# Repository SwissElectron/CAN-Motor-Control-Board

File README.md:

# **OpenSource CAN FD Compatible Motor Board**

This Board was designed as a part of a larger project in the making for a Robotic Arm Actuator System. The board can manipulate a BLDC motor from 24V to 48V (designed around LiPo battery packs) and with a max current rating of 20 A. 

## Board Information
- STM32F103 Central Microcontroller
- Sensor-less or Wioth Sensor Control strategies 
- 24V to 48V - 20 A
- Optional 5V rail for powering sensors on the CAN Bus

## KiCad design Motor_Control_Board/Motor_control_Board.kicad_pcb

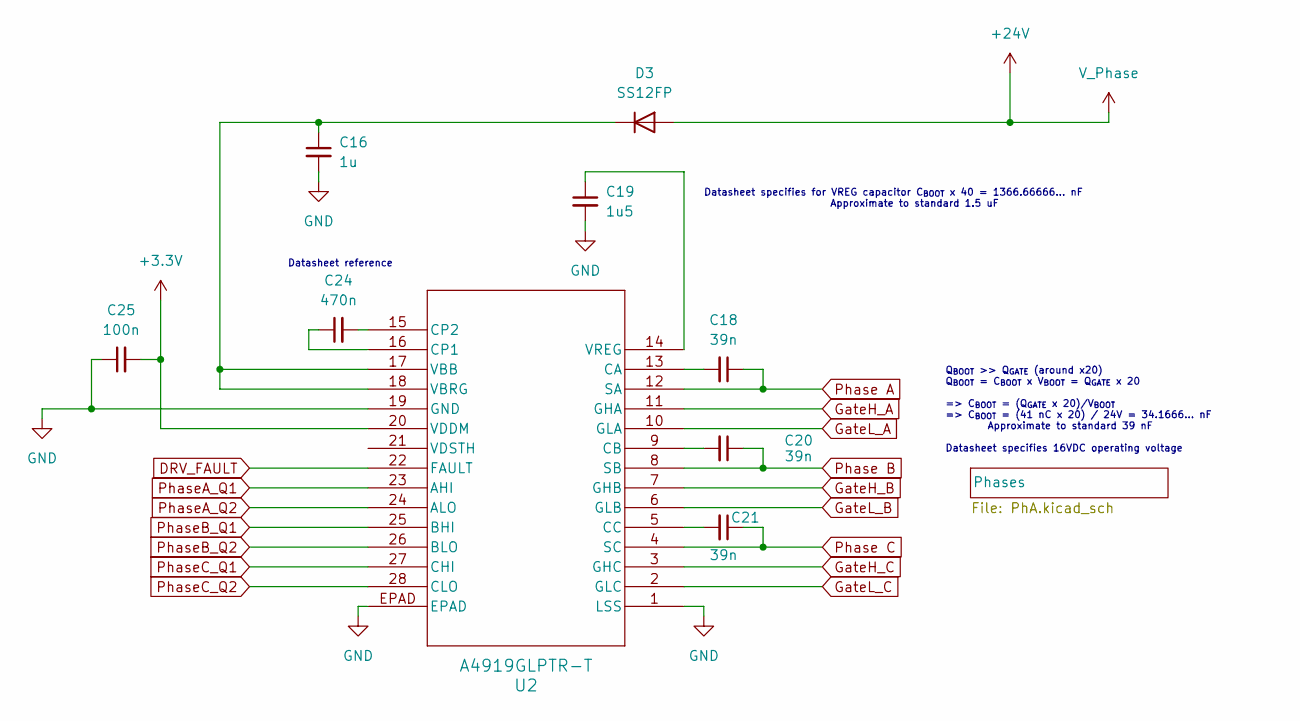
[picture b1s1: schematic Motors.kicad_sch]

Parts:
C16: 1u; C_0402_1005Metric; PartNum C1005X5R1C155K050BC
C18, C20, C21: 39n; C_0402_1005Metric; PartNum C0402C393J4RACTU
C19: 1u5; C_0402_1005Metric; PartNum C1005X5R1C155K050BC
C24: 470n; C_0603_1608Metric; PartNum CL10B474KO8NNWC
C25: 100n; C_0402_1005Metric; PartNum C0402C104K4PAC
D3: SS12FP; DIO_SS12LS_RVG; PartNum SS12FP
U2: A4919GLPTR-T; A4919GLPTR-T_ALM; PartNum A4919GLPTR-T

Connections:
+3.3V: C25.2, U2.20 (VDDM); also elsewhere on the board
DRV_FAULT: U2.22 (FAULT); also elsewhere on the board
GND: C16.2, C19.2, C25.1, U2.1 (LSS), U2.19 (GND), U2.EPAD; also elsewhere on the board
GateH_A: U2.11 (GHA); also elsewhere on the board
GateH_B: U2.7 (GHB); also elsewhere on the board
GateH_C: U2.3 (GHC); also elsewhere on the board
GateL_A: U2.10 (GLA); also elsewhere on the board
GateL_B: U2.6 (GLB); also elsewhere on the board
GateL_C: U2.2 (GLC); also elsewhere on the board
unnamed: C16.1, D3.1 (K), U2.17 (VBB), U2.18 (VBRG)
unnamed: C18.2, U2.13 (CA)
unnamed: C20.2, U2.9 (CB)
unnamed: C21.2, U2.5 (CC)
unnamed: C24.1, U2.16 (CP1)
unnamed: C24.2, U2.15 (CP2)
unnamed: C19.1, U2.14 (VREG)
Phase A: C18.1, U2.12 (SA); also elsewhere on the board
Phase B: C20.1, U2.8 (SB); also elsewhere on the board
Phase C: C21.1, U2.4 (SC); also elsewhere on the board
PhaseA_Q1: U2.23 (AHI); also elsewhere on the board
PhaseA_Q2: U2.24 (ALO); also elsewhere on the board
PhaseB_Q1: U2.25 (BHI); also elsewhere on the board
PhaseB_Q2: U2.26 (BLO); also elsewhere on the board
PhaseC_Q1: U2.27 (CHI); also elsewhere on the board
PhaseC_Q2: U2.28 (CLO); also elsewhere on the board

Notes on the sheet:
Q_{BOOT} >> Q_{GATE} (around x20) Q_{BOOT} = C_{BOOT} x V_{BOOT} = Q_{GATE} x 20 => C_{BOOT} = (Q_{GATE} x 20)/V_{BOOT} => C_{BOOT} = (41 nC x 20) / 24V = 34.1666... nF Approximate to standard 39 nF Datasheet specifies 16VDC operating voltage
Datasheet reference
Datasheet specifies for VREG capacitor C_{BOOT} x 40 = 1366.66666... nF Approximate to standard 1.5 uF

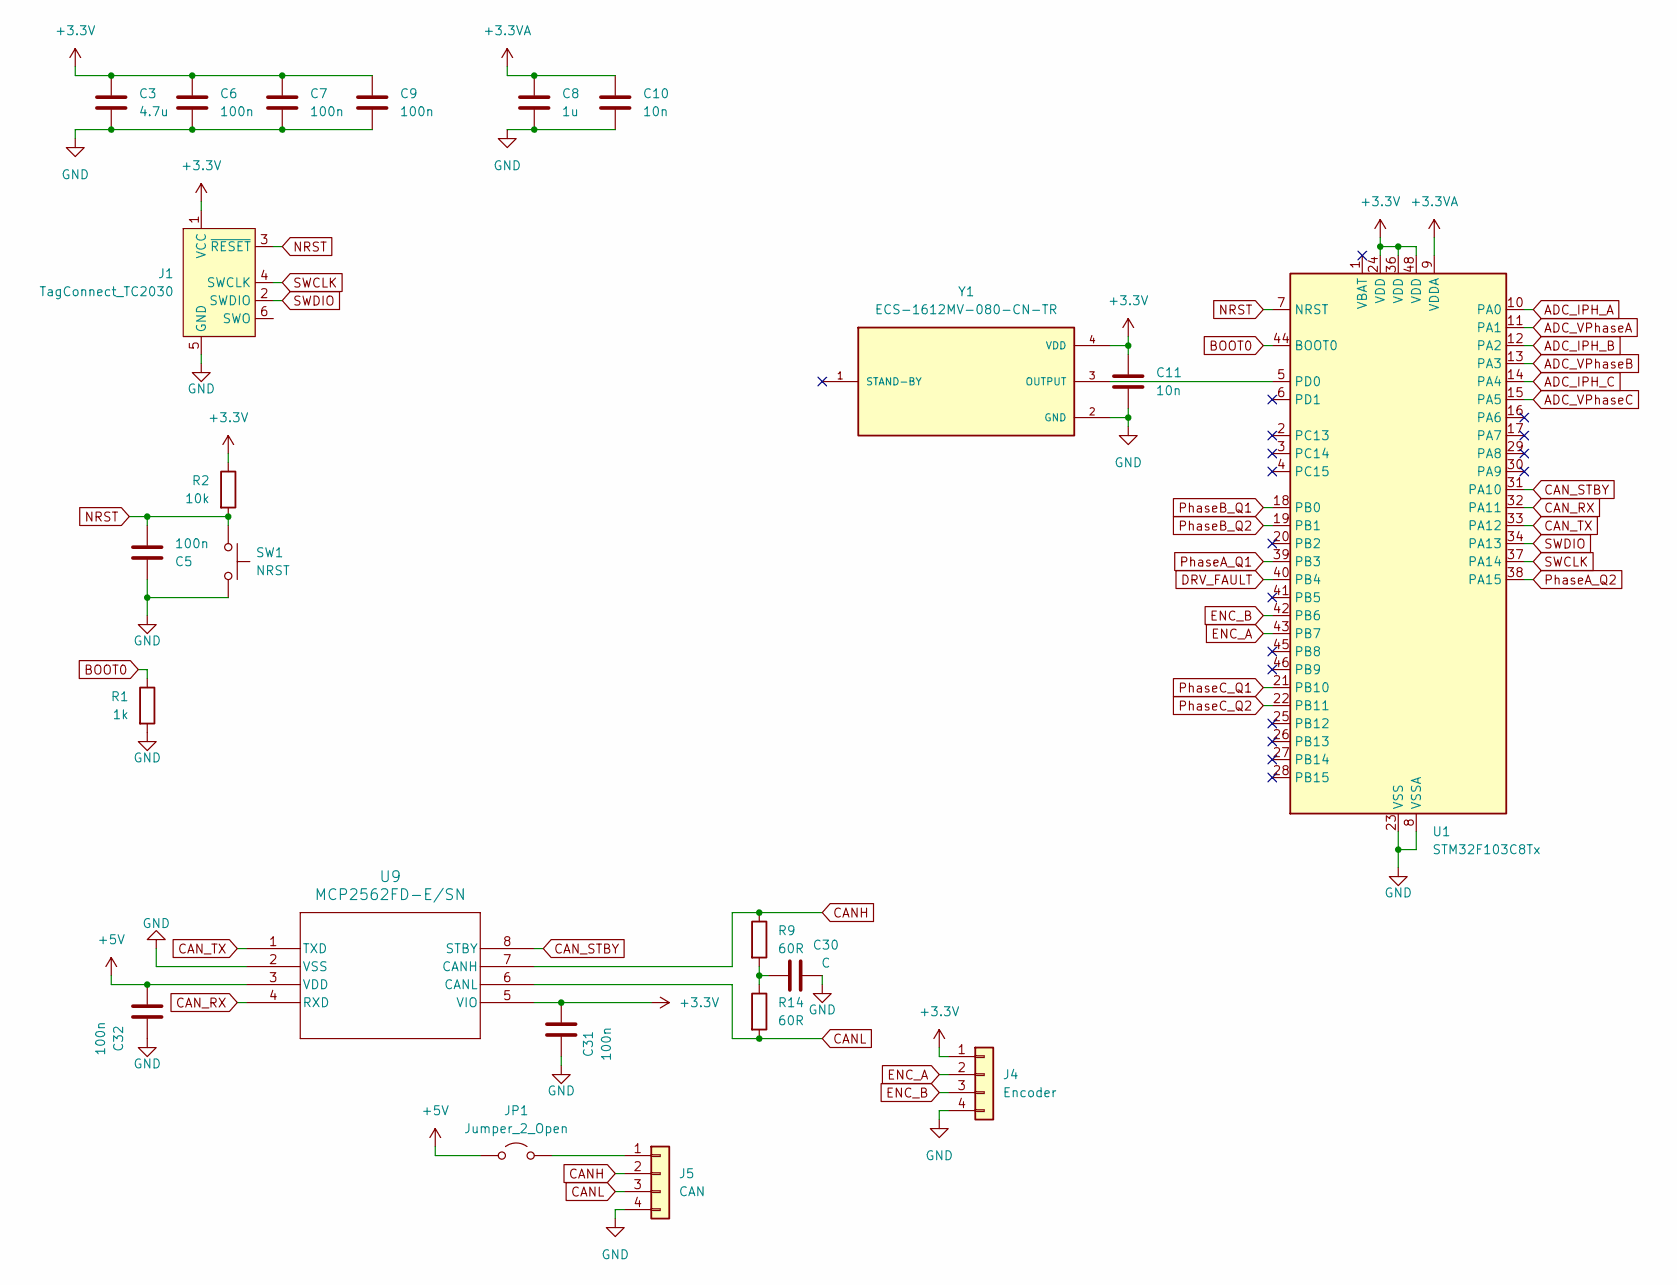
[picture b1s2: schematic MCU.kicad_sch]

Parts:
C3: 4.7u; C_0603_1608Metric; PartNum C0603C475M9PAC
C5, C6, C7, C9: 100n; C_0402_1005Metric; PartNum C0402C104K4PAC
C8: 1u; C_0402_1005Metric; PartNum GMD155R60J105KE11D
C10, C11: 10n; C_0402_1005Metric; PartNum GMD155R60J105KE11D
C30: C; C_0402_1005Metric
C31: 100n; C_0402_1005Metric; PartNum C0402C104K8RAC
C32: 100n; C_0402_1005Metric; PartNum GRM155R60J104MA01J
J1: TagConnect_TC2030; Tag-Connect_TC2030-IDC-NL_2x03_P1.27mm_Vertical
J4: Encoder; Molex_Pico-Clasp_501331-0407_1x04-1MP_P1.00mm_Vertical
J5: CAN; Molex_Pico-Clasp_501331-0407_1x04-1MP_P1.00mm_Vertical
JP1: Jumper_2_Open; SolderJumper-2_P1.3mm_Open_TrianglePad1.0x1.5mm
R1: 1k; C_0402_1005Metric; PartNum 0402WGF1001TCE
R2: 10k; R_0402_1005Metric; PartNum 0402WGF1002TCE
R9, R14: 60R; R_0402_1005Metric; PartNum 560112110170
SW1: NRST; NANOT100AS; PartNum NANOT100AS
U1: STM32F103C8Tx; LQFP-48_7x7mm_P0.5mm; PartNum STM32F103C8T7
U9: MCP2562FD-E/SN; MCP2562FD-ESN; PartNum MCP2562FD-E/SN
Y1: ECS-1612MV-080-CN-TR; OSC_ECS-1612MV-080-CN-TR-4; PartNum ECS-1612MV-080-CN-TR

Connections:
+3.3V: C3.1, C6.1, C7.1, C9.1, C11.1, C31.2, J1.1 (VCC), J4.1, R2.1, U1.24 (VDD), U1.36 (VDD), U1.48 (VDD), U9.5 (VIO), Y1.4 (VDD); also elsewhere on the board
+3.3VA: C8.1, C10.1, U1.9 (VDDA); also elsewhere on the board
+5V: C32.1, JP1.1 (A), U9.3 (VDD); also elsewhere on the board
ADC_IPH_A: U1.10 (PA0); also elsewhere on the board
ADC_IPH_B: U1.12 (PA2); also elsewhere on the board
ADC_IPH_C: U1.14 (PA4); also elsewhere on the board
ADC_VPhaseA: U1.11 (PA1); also elsewhere on the board
ADC_VPhaseB: U1.13 (PA3); also elsewhere on the board
ADC_VPhaseC: U1.15 (PA5); also elsewhere on the board
BOOT0: R1.1, U1.44 (BOOT0)
CANH: J5.2, R9.1, U9.7 (CANH)
CANL: J5.3, R14.2, U9.6 (CANL)
CAN_RX: U1.32 (PA11), U9.4 (RXD)
CAN_STBY: U1.31 (PA10), U9.8 (STBY)
CAN_TX: U1.33 (PA12), U9.1 (TXD)
DRV_FAULT: U1.40 (PB4); also elsewhere on the board
ENC_A: J4.2, U1.43 (PB7)
ENC_B: J4.3, U1.42 (PB6)
GND: C3.2, C5.1, C6.2, C7.2, C8.2, C9.2, C10.2, C11.2, C30.2, C31.1, C32.2, J1.5 (GND), J4.4, J5.4, R1.2, SW1.2, U1.8 (VSSA), U1.23 (VSS), U1.35 (VSS), U1.47 (VSS), U9.2 (VSS), Y1.2 (GND); also elsewhere on the board
NRST: C5.2, J1.3 (~RESET), R2.2, SW1.1, U1.7 (NRST)
unnamed: C30.1, R9.2, R14.1
unnamed 31: J5.1, JP1.2 (B); also elsewhere on the board
unnamed: U1.5 (PD0), Y1.3 (OUTPUT)
PhaseA_Q1: U1.39 (PB3); also elsewhere on the board
PhaseA_Q2: U1.38 (PA15); also elsewhere on the board
PhaseB_Q1: U1.18 (PB0); also elsewhere on the board
PhaseB_Q2: U1.19 (PB1); also elsewhere on the board
PhaseC_Q1: U1.21 (PB10); also elsewhere on the board
PhaseC_Q2: U1.22 (PB11); also elsewhere on the board
SWCLK: J1.4 (SWCLK), U1.37 (PA14)
SWDIO: J1.2 (SWDIO), U1.34 (PA13)

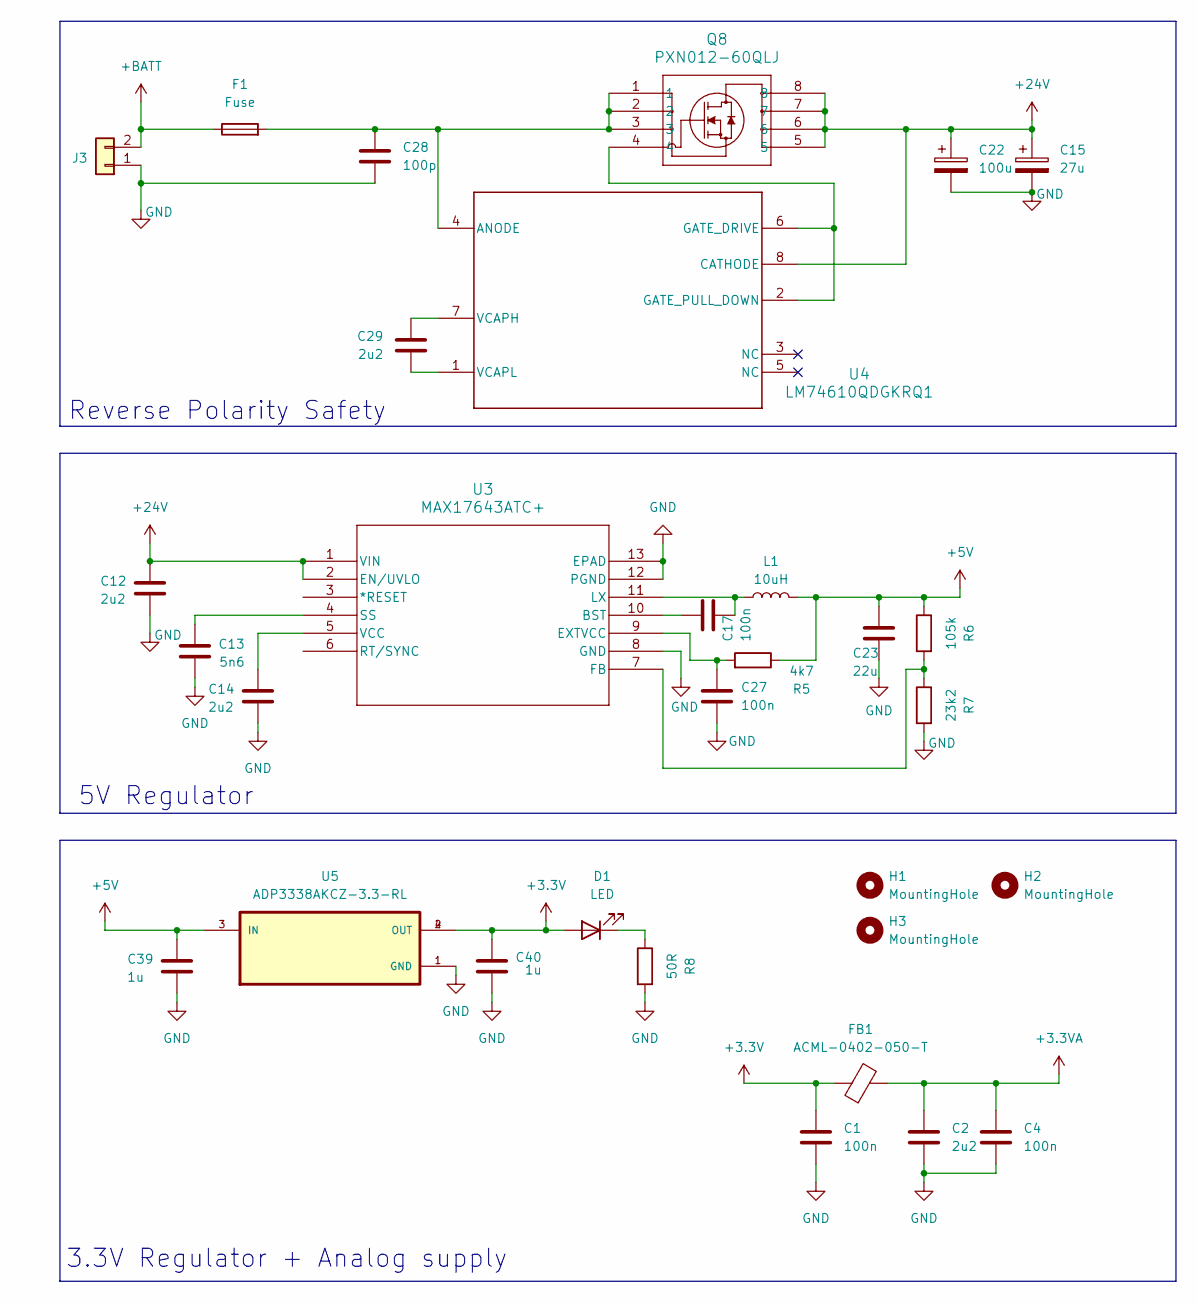
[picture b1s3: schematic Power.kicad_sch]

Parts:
C1, C4: 100n; C_0402_1005Metric; PartNum GCM1555C1H240FA16J
C2: 2u2; C_1206_3216Metric; PartNum C1206C225M5REC7210
C12: 2u2; C_1210_3225Metric; PartNum GRM32ER72A225KA35L
C13: 5n6; C_0402_1005Metric; PartNum GMD155R60J105KE11D
C14, C29: 2u2; C_0603_1608Metric; PartNum GRM188R71A225KE15
C15: 27u; CP_Elec_6.3x7.7; PartNum UUD1H270MCL1GS
C17, C27: 100n; C_0402_1005Metric; PartNum GMD155R60J105KE11D
C22: 100u; CP_Elec_8x10; PartNum UWT1H101MNL1GS
C23: 22u; C_1210_3225Metric; PartNum GRM32ER71C226KEA8
C28: 100p; C_0402_1005Metric; PartNum GRM0225C1H101JA02L
C39, C40: 1u; C_0402_1005Metric; PartNum GMD155R60J105KE11D
D1: LED; LED_0402_1005Metric; PartNum LTST-C281KGKT
F1: Fuse; Fuse_1206_3216Metric; PartNum SF-1206HH3000R-2
FB1: ACML-0402-050-T; L_0402_1005Metric; PartNum ACML-0402-050-T
H1, H2, H3: MountingHole; MountingHole_3.2mm_M3_DIN965
J3: Conn_01x02; AMASS_XT60-M
L1: 10uH; L_Coilcraft_XAL5050-XXX; PartNum XAL5050-103MEC
Q8: PXN012-60QLJ; PartNum PXN012-60QLJ
R5: 4k7; R_0402_1005Metric; PartNum HP02WAJ0472TCE
R6: 105k; R_0402_1005Metric; PartNum RC0402FR-07105KL
R7: 23k2; R_0402_1005Metric; PartNum CRCW040223K2FKED
R8: 50R; R_0402_1005Metric; PartNum RC0402JR-0750RL
U3: MAX17643ATC+; MAX17643; PartNum MAX17643ATC+
U4: LM74610QDGKRQ1; PartNum LM74610QDGKRQ1
U5: ADP3338AKCZ-3.3-RL; ADP3338AKCz-3.3; PartNum ADP3338AKCZ-3.3-RL

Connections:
+3.3V: C1.1, C40.2, D1.2 (A), FB1.1, U5.2 (OUT), U5.4 (OUT); also elsewhere on the board
+3.3VA: C2.1, C4.1, FB1.2; also elsewhere on the board
+5V: C23.1, C39.1, L1.2, R5.1, R6.1, U5.3 (IN); also elsewhere on the board
+24V: C12.1, C15.1, C22.1, Q8.5, Q8.6, Q8.7, Q8.8, U3.1 (VIN), U3.2 (EN/UVLO), U4.8 (CATHODE); also elsewhere on the board
+BATT: F1.1, J3.2
GND: C1.2, C2.2, C4.2, C12.2, C13.2, C14.2, C15.2, C22.2, C23.2, C27.2, C28.2, C39.2, C40.1, J3.1, R7.2, R8.2, U3.8 (GND), U3.12 (PGND), U3.13 (EPAD), U5.1 (GND); also elsewhere on the board
unnamed: D1.1 (K), R8.1
unnamed: C17.1, U3.10 (BST)
unnamed: C27.1, R5.2, U3.9 (EXTVCC)
unnamed: R6.2, R7.1, U3.7 (FB)
unnamed: C17.2, L1.1, U3.11 (LX)
unnamed: C13.1, U3.4 (SS)
unnamed: C14.1, U3.5 (VCC)
unnamed: C28.1, F1.2, Q8.1, Q8.2, Q8.3, U4.4 (ANODE)
unnamed: Q8.4, U4.2 (GATE_PULL_DOWN), U4.6 (GATE_DRIVE)
unnamed: C29.1, U4.7 (VCAPH)
unnamed: C29.2, U4.1 (VCAPL)

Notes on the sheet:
Reverse Polarity Safety
3.3V Regulator + Analog supply
5V Regulator

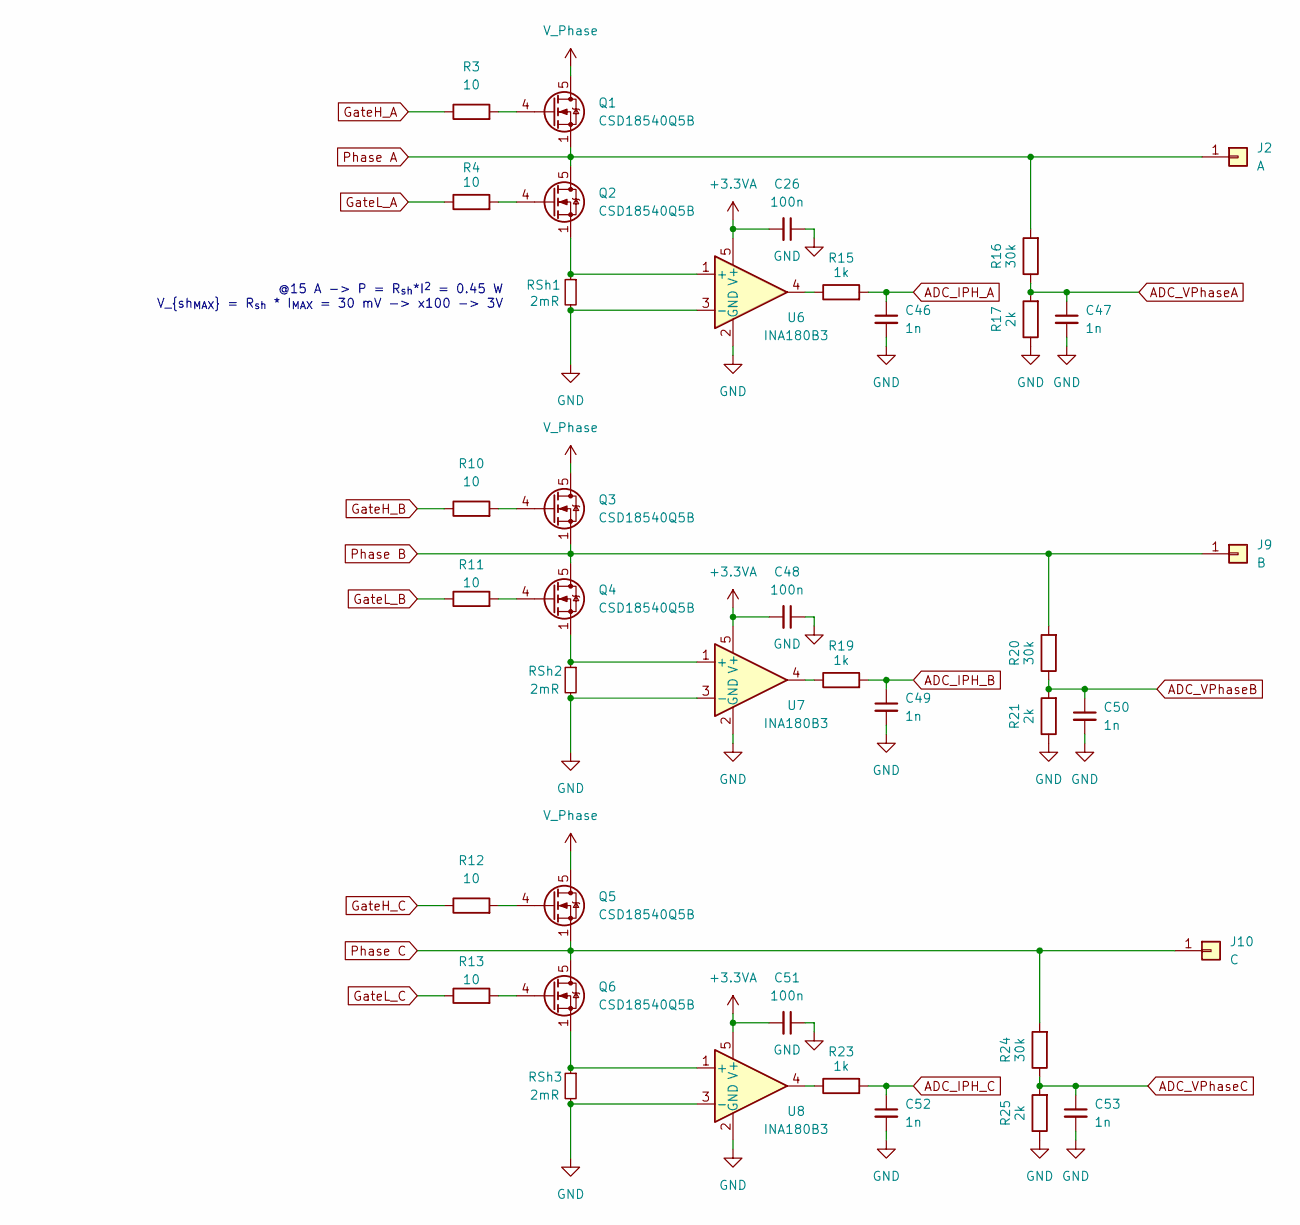
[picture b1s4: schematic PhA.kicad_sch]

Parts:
C26, C48, C51: 100n; C_0402_1005Metric; PartNum C0402C104K4PAC
C46, C47, C49, C50, C52, C53: 1n; C_0402_1005Metric; PartNum 885012005018
J2: A; Pin_D1.1mm_L8.5mm_W2.5mm_FlatFork
J9: B; Pin_D1.1mm_L8.5mm_W2.5mm_FlatFork
J10: C; Pin_D1.1mm_L8.5mm_W2.5mm_FlatFork
Q1, Q2, Q3, Q4, Q5, Q6: CSD18540Q5B; TDSON-8-1; PartNum CSD18540Q5B
R3, R4, R10, R11, R12, R13: 10; R_0603_1608Metric; PartNum PCAN0603E10R0BST3
R15, R19, R23: 1k; C_0402_1005Metric; PartNum 0402WGF1001TCE
R16, R20, R24: 30k; R_0402_1005Metric; PartNum CQ02WGF1272TCE
R17, R21, R25: 2k; R_0402_1005Metric; PartNum HP02WAJ0202TCE
RSh1, RSh2, RSh3: 2mR; R_0805_2012Metric; PartNum L4CL2512LR002FYR
U6, U7, U8: INA180B3; SOT-23-5; PartNum INA180B3QDBVRQ1

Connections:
+3.3VA: C26.2, C48.2, C51.2, U6.5 (V+), U7.5 (V+), U8.5 (V+); also elsewhere on the board
+24V: Q1.5 (D), Q3.5 (D), Q5.5 (D); also elsewhere on the board
ADC_IPH_A: C46.1, R15.2; also elsewhere on the board
ADC_IPH_B: C49.1, R19.2; also elsewhere on the board
ADC_IPH_C: C52.1, R23.2; also elsewhere on the board
ADC_VPhaseA: C47.1, R16.1, R17.2; also elsewhere on the board
ADC_VPhaseB: C50.1, R20.1, R21.2; also elsewhere on the board
ADC_VPhaseC: C53.1, R24.1, R25.2; also elsewhere on the board
GND: C26.1, C46.2, C47.2, C48.1, C49.2, C50.2, C51.1, C52.2, C53.2, R17.1, R21.1, R25.1, RSh1.2, RSh2.2, RSh3.2, U6.2 (GND), U6.3 (-), U7.2 (GND), U7.3 (-), U8.2 (GND), U8.3 (-); also elsewhere on the board
GateH_A: R3.1; also elsewhere on the board
GateH_B: R10.1; also elsewhere on the board
GateH_C: R12.1; also elsewhere on the board
GateL_A: R4.1; also elsewhere on the board
GateL_B: R11.1; also elsewhere on the board
GateL_C: R13.1; also elsewhere on the board
unnamed: Q1.4 (G), R3.2
unnamed: Q2.4 (G), R4.2
unnamed: Q3.4 (G), R10.2
unnamed: Q4.4 (G), R11.2
unnamed: Q5.4 (G), R12.2
unnamed: Q6.4 (G), R13.2
unnamed: R15.1, U6.4
unnamed: R19.1, U7.4
unnamed: R23.1, U8.4
unnamed: Q2.1 (S), Q2.2 (S), Q2.3 (S), RSh1.1, U6.1 (+)
unnamed: Q4.1 (S), Q4.2 (S), Q4.3 (S), RSh2.1, U7.1 (+)
unnamed: Q6.1 (S), Q6.2 (S), Q6.3 (S), RSh3.1, U8.1 (+)
Phase A: J2.1, Q1.1 (S), Q1.2 (S), Q1.3 (S), Q2.5 (D), R16.2; also elsewhere on the board
Phase B: J9.1, Q3.1 (S), Q3.2 (S), Q3.3 (S), Q4.5 (D), R20.2; also elsewhere on the board
Phase C: J10.1, Q5.1 (S), Q5.2 (S), Q5.3 (S), Q6.5 (D), R24.2; also elsewhere on the board

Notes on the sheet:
@15 A -> P = R_{sh}*I^{2} = 0.45 W V_{sh_{MAX}} = R_{sh} * I_{MAX} = 30 mV -> x100 -> 3V

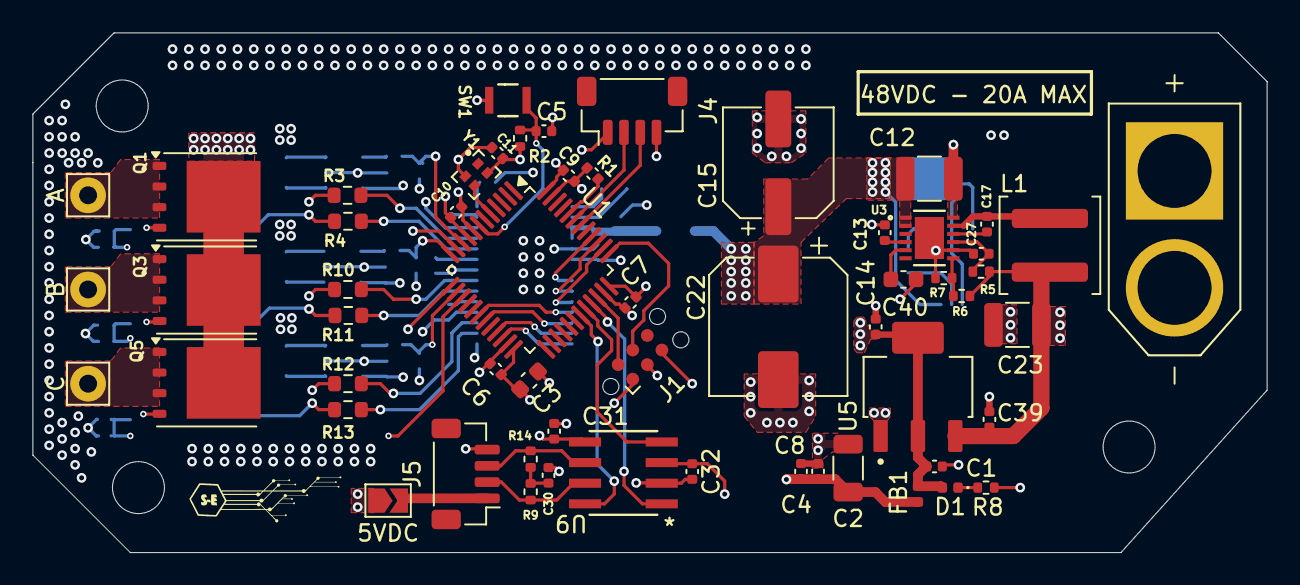
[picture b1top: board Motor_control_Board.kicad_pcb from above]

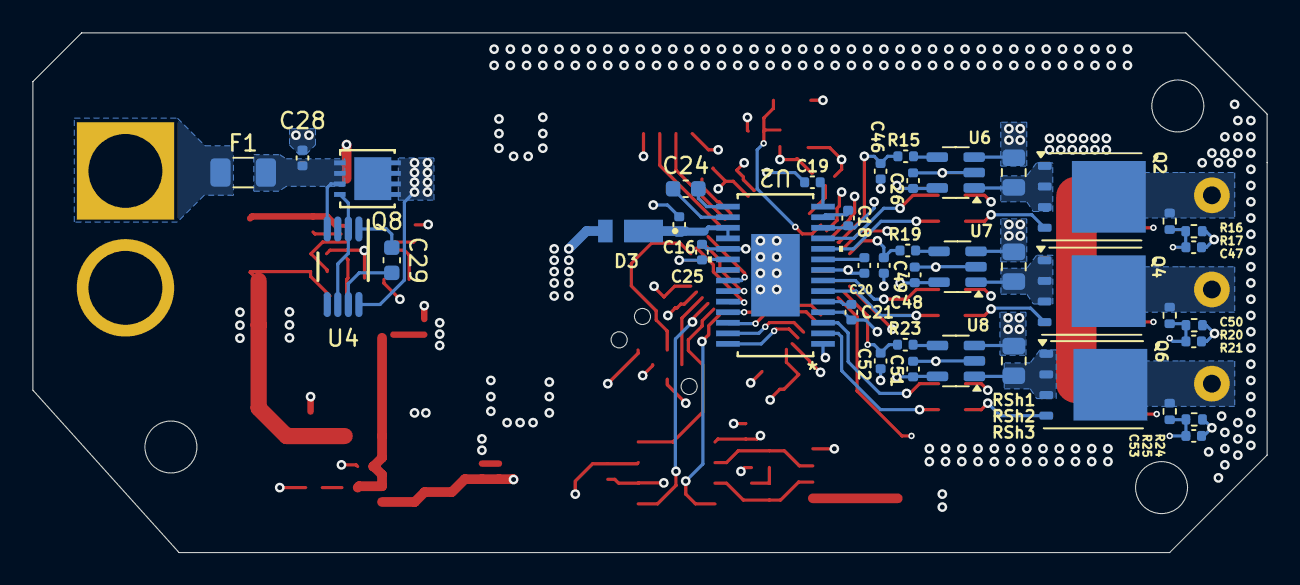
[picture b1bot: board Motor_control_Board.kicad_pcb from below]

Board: 4 copper layers, 76.0 x 32.0 mm, 102 parts (41 on the bottom side), 71 nets.

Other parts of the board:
5VDC: Jumper_2_Open; SolderJumper-2_P1.3mm_Open_TrianglePad1.0x1.5mm
A: A; Pin_D1.1mm_L8.5mm_W2.5mm_FlatFork
B: B; Pin_D1.1mm_L8.5mm_W2.5mm_FlatFork
C: C; Pin_D1.1mm_L8.5mm_W2.5mm_FlatFork

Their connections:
+5V: 5VDC.1 (A); also elsewhere on the board
unnamed 31: 5VDC.2 (B); also elsewhere on the board
Phase A: A.1; also elsewhere on the board
Phase B: B.1; also elsewhere on the board
Phase C: C.1; also elsewhere on the board

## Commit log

2025-02-05 Initial Commit: V0.8
2025-02-05 Added README file
2025-02-06 Minor updates: V0.9
2025-02-06 Added Documentation
2025-02-20 V0.10 - chnaged Volatge Sensing resistors to enable 48V sensing
